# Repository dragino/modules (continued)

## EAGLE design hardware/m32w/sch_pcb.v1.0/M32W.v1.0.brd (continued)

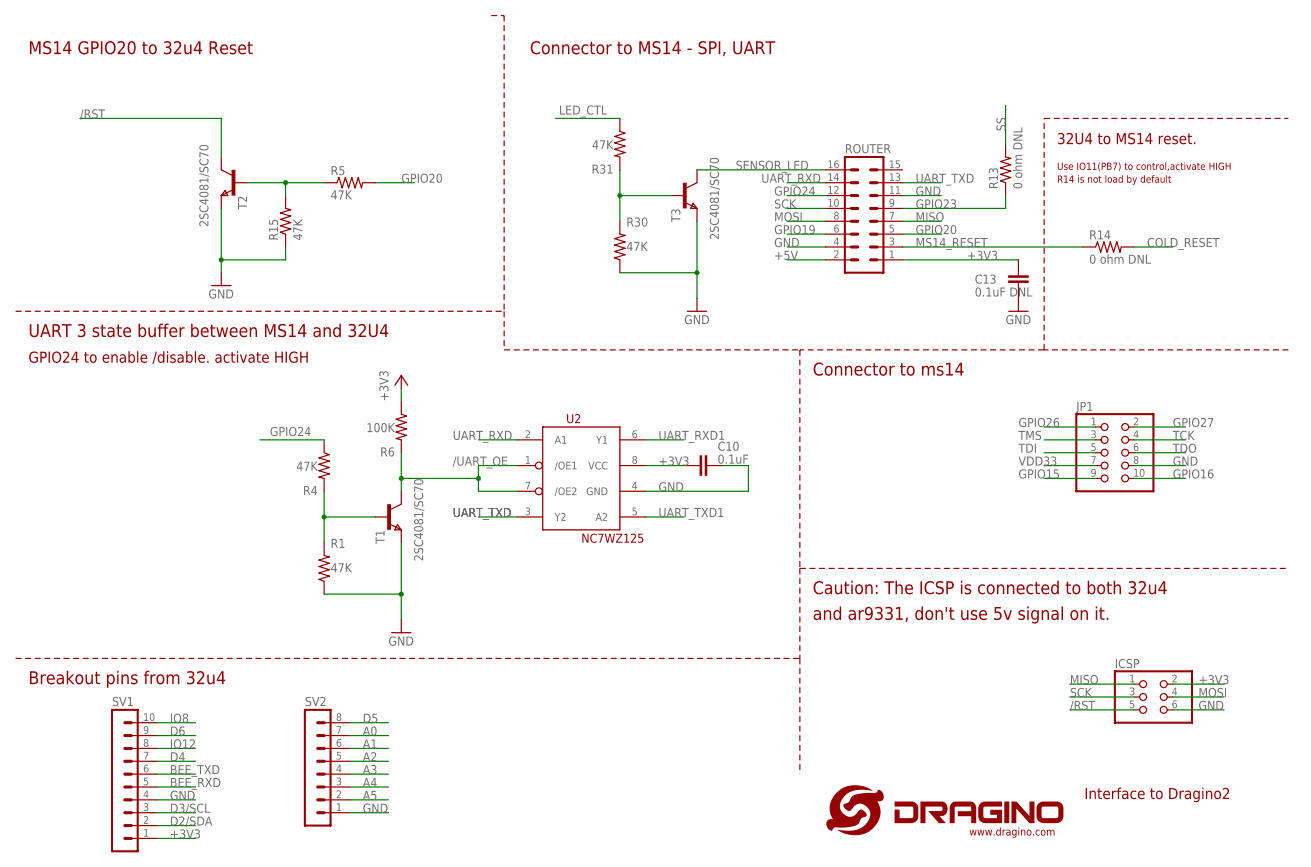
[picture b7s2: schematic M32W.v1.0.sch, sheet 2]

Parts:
C10: 0.1uF; C0402
C13: 0.1uF DNL; C0402
ICSP: PINHD-2X3; 2X03
JP1: PINHD-2X5_2.00; 2X05M
R1, R4, R5, R15, R30, R31: 47K; R0402
R6: 100K; R0402
R13, R14: 0 ohm DNL; R0402
ROUTER: MA08-2
SV1: MA10-1
SV2: MA08-1
T1, T3: 2SC4081/SC70; SOT323
T2: 2SC4081/SC70; SOT323; MPN DSS4160U-7
U2: NC7WZ125; US8
U$5: LOGO-NEW; LOGO-SILK-NEW

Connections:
+3V3: C10.2, C13.1, ICSP.2, R6.1, ROUTER.1, SV1.1, U2.8 (VCC); also elsewhere on the board
+5V: ROUTER.2
/RST: ICSP.5, T2.1 (C); also elsewhere on the board
/UART_OE: R6.2, T1.1 (C), U2.1 (/OE1), U2.7 (/OE2)
A0: SV2.7; also elsewhere on the board
A1: SV2.6; also elsewhere on the board
A2: SV2.5; also elsewhere on the board
A3: SV2.4; also elsewhere on the board
A4: SV2.3; also elsewhere on the board
A5: SV2.2; also elsewhere on the board
BEE_RXD: SV1.5; also elsewhere on the board
BEE_TXD: SV1.6; also elsewhere on the board
COLD_RESET: R14.2; also elsewhere on the board
D2/SDA: SV1.2; also elsewhere on the board
D3/SCL: SV1.3; also elsewhere on the board
D4: SV1.7; also elsewhere on the board
D5: SV2.8; also elsewhere on the board
D6: SV1.9; also elsewhere on the board
GND: C10.1, C13.2, ICSP.6, JP1.8, R1.1, R15.1, R30.1, ROUTER.4, ROUTER.11, SV1.4, SV2.1, T1.3 (E), T2.3 (E), T3.3 (E), U2.4 (GND); also elsewhere on the board
GPIO15: JP1.9
GPIO16: JP1.10
GPIO19: ROUTER.6
GPIO20: R5.2, ROUTER.5
GPIO23: R13.1, ROUTER.9
GPIO24: R4.1, ROUTER.12
GPIO26: JP1.1; also elsewhere on the board
GPIO27: JP1.2; also elsewhere on the board
IO8: SV1.10; also elsewhere on the board
IO12: SV1.8; also elsewhere on the board
LED_CTL: R31.1; also elsewhere on the board
MISO: ICSP.1, ROUTER.7; also elsewhere on the board
MOSI: ICSP.4, ROUTER.8; also elsewhere on the board
MS14_RESET: R14.1, ROUTER.3
unnamed: R1.2, R4.2, T1.2 (B)
unnamed: R5.1, R15.2, T2.2 (B)
unnamed: R30.2, R31.2, T3.2 (B)
SCK: ICSP.3, ROUTER.10; also elsewhere on the board
SENSOR_LED: ROUTER.16, T3.1 (C)
SS: R13.2; also elsewhere on the board
TCK: JP1.4
TDI: JP1.5
TDO: JP1.6
TMS: JP1.3
UART_RXD: ROUTER.14, U2.2 (A1); also elsewhere on the board
UART_RXD1: U2.6 (Y1); also elsewhere on the board
UART_TXD: ROUTER.13, U2.3 (Y2); also elsewhere on the board
UART_TXD1: U2.5 (A2); also elsewhere on the board
VDD33: JP1.7

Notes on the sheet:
UART 3 state buffer between MS14 and 32U4
Interface to Dragino2
Caution: The ICSP is connected to both 32u4
and ar9331, don't use 5v signal on it.
Connector to ms14
Connector to MS14 - SPI, UART
MS14 GPIO20 to 32u4 Reset
Breakout pins from 32u4
GPIO24 to enable /disable. activate HIGH
32U4 to MS14 reset.
Use IO11(PB7) to control,activate HIGH
R14 is not load by default

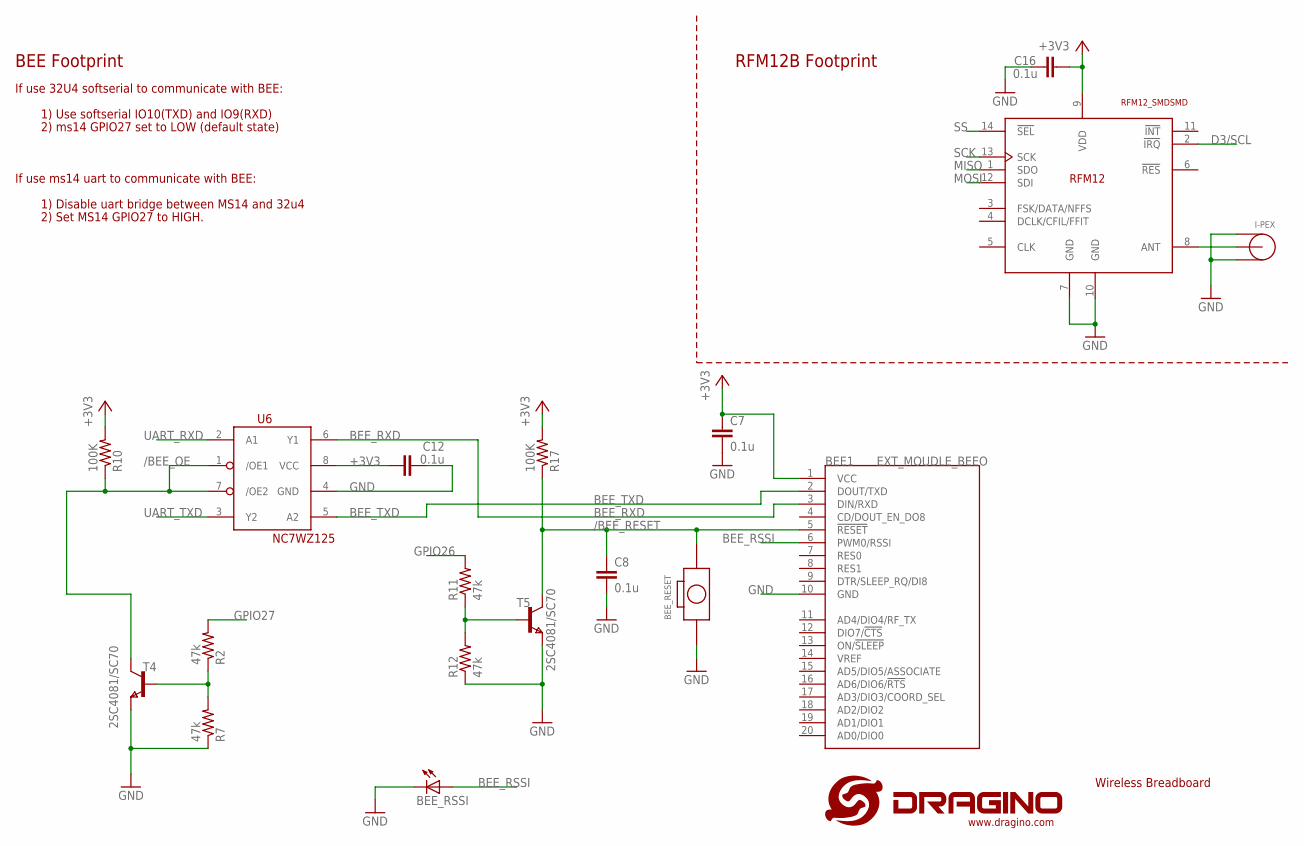
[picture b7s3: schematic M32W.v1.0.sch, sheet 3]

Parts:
BEE1: EXT_MOUDLE_BEEO; EXT_MOUDLE_BEE
BEE_RESET: CPT_SMD_BOTTON_1_SMD; CPT_SMD_BOTTON_1
BEE_RSSI: LEDCHIP-LED0805; CHIP-LED0805
C7, C8, C12, C16: 0.1u; C0402
I-PEX: I-PEX
R2, R7, R11, R12: 47k; R0402
R10, R17: 100K; R0402
T4, T5: 2SC4081/SC70; SOT323
U6: NC7WZ125; US8
U$3: RFM12_SMDSMD; RFM12

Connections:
+3V3: BEE1.1 (VCC), C7.1, C12.1, C16.2, R10.2, R17.2, U6.8 (VCC), U$3.9 (VDD); also elsewhere on the board
/BEE_OE: R10.1, T4.1 (C), U6.1 (/OE1), U6.7 (/OE2)
/BEE_RESET: BEE1.5 (!RESET), BEE_RESET.P$2 (2), C8.1, R17.1, T5.1 (C)
BEE_RSSI: BEE1.6 (PWM0/RSSI), BEE_RSSI.A
BEE_RXD: BEE1.3 (DIN/RXD), U6.6 (Y1); also elsewhere on the board
BEE_TXD: BEE1.2 (DOUT/TXD), U6.5 (A2); also elsewhere on the board
D3/SCL: U$3.2 (!IRQ); also elsewhere on the board
GND: BEE1.10 (GND), BEE_RESET.1, BEE_RSSI.C, C7.2, C8.2, C12.2, C16.1, I-PEX.GND, I-PEX.GND1, R7.1, R12.1, T4.3 (E), T5.3 (E), U6.4 (GND), U$3.7 (GND), U$3.10 (GND); also elsewhere on the board
GPIO26: R11.2; also elsewhere on the board
GPIO27: R2.2; also elsewhere on the board
MISO: U$3.1 (SDO); also elsewhere on the board
MOSI: U$3.12 (SDI); also elsewhere on the board
unnamed: R2.1, R7.2, T4.2 (B)
unnamed: R11.1, R12.2, T5.2 (B)
unnamed: I-PEX.SIG, U$3.8 (ANT)
SCK: U$3.13 (SCK); also elsewhere on the board
SS: U$3.14 (!SEL); also elsewhere on the board
UART_RXD: U6.2 (A1); also elsewhere on the board
UART_TXD: U6.3 (Y2); also elsewhere on the board

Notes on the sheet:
Wireless Breadboard
RFM12B Footprint
BEE Footprint
If use 32U4 softserial to communicate with BEE:
1) Use softserial IO10(TXD) and IO9(RXD)
2) ms14 GPIO27 set to LOW (default state)
If use ms14 uart to communicate with BEE:
1) Disable uart bridge between MS14 and 32u4
2) Set MS14 GPIO27 to HIGH.

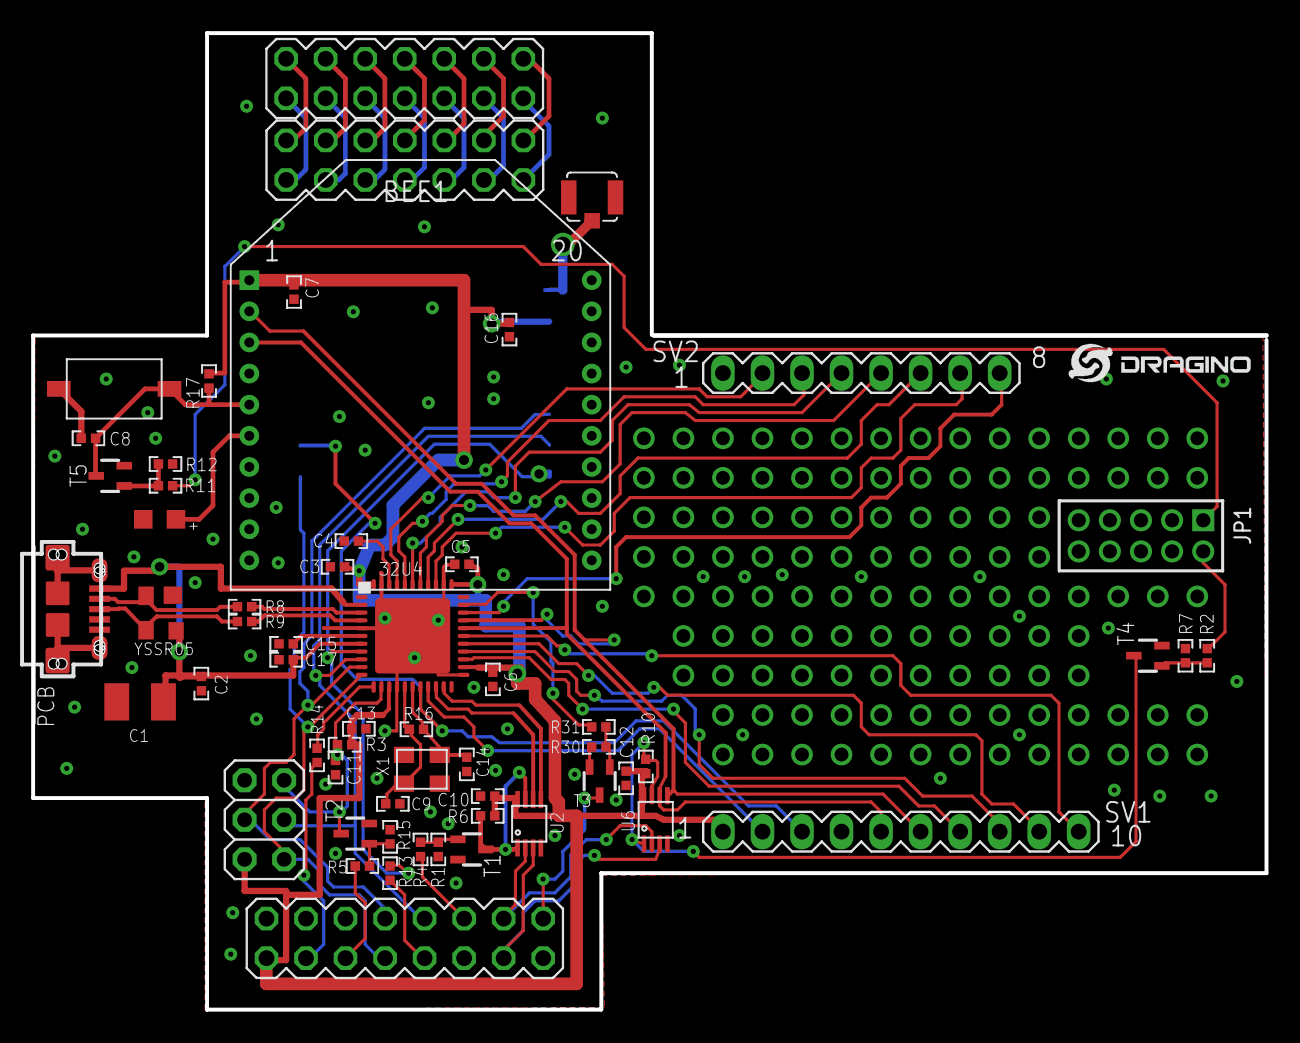
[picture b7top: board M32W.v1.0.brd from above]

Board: 2 copper layers, 79.2 x 62.7 mm, 60 parts (1 on the bottom side), 68 nets.

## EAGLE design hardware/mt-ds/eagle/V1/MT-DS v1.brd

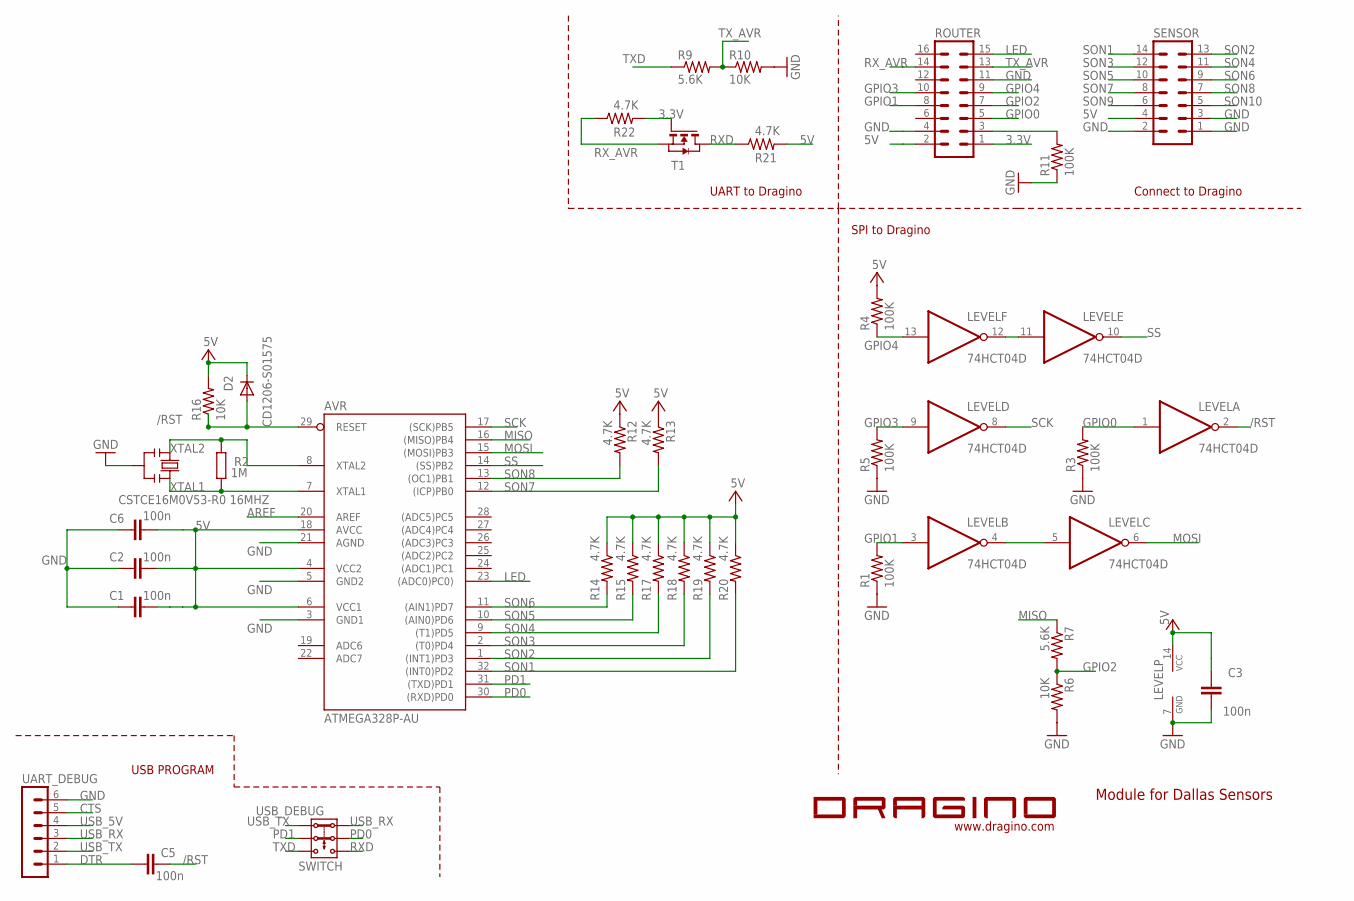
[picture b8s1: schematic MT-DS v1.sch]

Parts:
AVR: ATMEGA328P-AU; SMARTPRJ_TQFP32-08
C1, C2, C3, C5, C6: 100n; C0402
D2: CD1206-S01575; MINIMELF
LEVEL: 74HCT04D; SO14
R1, R3, R4, R5, R11: 100K; R0402
R2: 1M; R0402
R6, R10, R16: 10K; R0402
R7, R9: 5.6K; R0402
R12, R13, R14, R15, R17, R18, R19, R20, R21, R22: 4.7K; R0805
ROUTER: MA08-2
SENSOR: MA07-2
T1: NMOSFET-SOT23; SOT-23
U$1: LOGO-SILK; LOGO-SILK-15MM
UART_DEBUG: MA06-1
USB_DEBUG: SWITCH; 2P2T
Y2: CSTCE16M0V53-R0 16MHZ; RESONATOR

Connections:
3.3V: R22.2, ROUTER.1, T1.3 (G)
5V: AVR.4 (VCC2), AVR.6 (VCC1), AVR.18 (AVCC), C1.1, C2.1, C3.2, C6.1, D2.C, LEVEL.14 (VCC), R4.2, R12.1, R13.1, R14.1, R15.1, R16.2, R17.1, R18.1, R19.1, R20.1, R21.2, ROUTER.2, SENSOR.4
/RST: AVR.29 (RESET), C5.2, D2.A, LEVEL.2 (O), R16.1
AREF: AVR.20 (AREF)
CTS: UART_DEBUG.5
DTR: C5.1, UART_DEBUG.1
GND: AVR.3 (GND1), AVR.5 (GND2), AVR.21 (AGND), C1.2, C2.2, C3.1, C6.2, LEVEL.7 (GND), R1.1, R3.1, R5.1, R6.2, R10.2, R11.1, ROUTER.4, ROUTER.11, SENSOR.1, SENSOR.2, SENSOR.3, UART_DEBUG.6, Y2.2
GPIO0: LEVEL.1 (I), R3.2, ROUTER.5
GPIO1: LEVEL.3 (I), R1.2, ROUTER.8
GPIO2: R6.1, R7.2, ROUTER.7
GPIO3: LEVEL.9 (I), R5.2, ROUTER.10
GPIO4: LEVEL.13 (I), R4.1, ROUTER.9
LED: AVR.23 ((ADC0)PC0)), ROUTER.15
MISO: AVR.16 ((MISO)PB4), R7.1
MOSI: AVR.15 ((MOSI)PB3), LEVEL.6 (O)
unnamed: R11.2, ROUTER.3
unnamed: LEVEL.11 (I), LEVEL.12 (O)
unnamed: LEVEL.4 (O), LEVEL.5 (I)
PD0: AVR.30 ((RXD)PD0), USB_DEBUG.2.1
PD1: AVR.31 ((TXD)PD1), USB_DEBUG.2.2
RXD: R21.1, T1.1 (D), USB_DEBUG.3.1
RX_AVR: R22.1, ROUTER.14, T1.2 (S)
SCK: AVR.17 ((SCK)PB5), LEVEL.8 (O)
SON1: AVR.32 ((INT0)PD2), R20.2, SENSOR.14
SON2: AVR.1 ((INT1)PD3), R19.2, SENSOR.13
SON3: AVR.2 ((T0)PD4), R18.2, SENSOR.12
SON4: AVR.9 ((T1)PD5), R17.2, SENSOR.11
SON5: AVR.10 ((AIN0)PD6), R15.2, SENSOR.10
SON6: AVR.11 ((AIN1)PD7), R14.2, SENSOR.9
SON7: AVR.12 ((ICP)PB0), R13.2, SENSOR.8
SON8: AVR.13 ((OC1)PB1), R12.2, SENSOR.7
SON9: SENSOR.6
SON10: SENSOR.5
SS: AVR.14 ((SS)PB2), LEVEL.10 (O)
TXD: R9.1, USB_DEBUG.3.2
TX_AVR: R9.2, R10.1, ROUTER.13
USB_5V: UART_DEBUG.4
USB_RX: UART_DEBUG.3, USB_DEBUG.1.1
USB_TX: UART_DEBUG.2, USB_DEBUG.1.2
XTAL1: AVR.7 (XTAL1), R2.1, Y2.3
XTAL2: AVR.8 (XTAL2), R2.2, Y2.1

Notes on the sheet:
Connect to Dragino
SPI to Dragino
UART to Dragino
USB PROGRAM
Module for Dallas Sensors

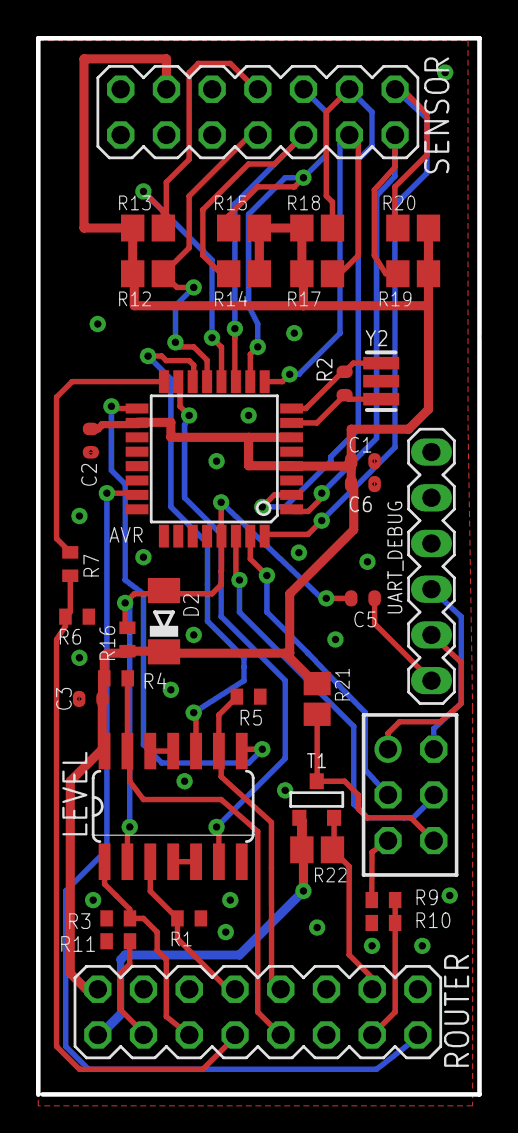
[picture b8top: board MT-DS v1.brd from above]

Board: 2 copper layers, 24.5 x 58.7 mm, 36 parts (0 on the bottom side), 36 nets.

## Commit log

2013-09-17 move files from dragino svn to git
2013-10-02 Add MS14 Bridge Example for Arduino Yun
2013-10-05 Add bridge example
2013-10-06 Add tested examples
    All are tested with ms14 + Lenonard
2013-10-07 Add Tested Example for Yun
2013-10-15 Add Tested Example for demo Yun + RFM12B
2013-10-16 Update Xively / Yeelink examples
    New example works with mega168 as well. Try to call linux script to
    upload sensor data.
2013-11-21 update sketch to better fit mrfm12b
2013-11-22 Add Sensor Projects
2013-11-25 update datalog example
2013-11-27 add example
    example: use a switch to control remote relay
2013-12-01 add m32 source
2013-12-06 Example to send daily report via Email
2013-12-06 ooops
2013-12-07 miss two pages.
2013-12-11 Serial LCD example- Remote control
    use REST calls to control a LCD
2014-01-21 Add M32 Silkscreen
2014-02-10 Add Cumulocity Client Demo
2014-02-24 add Cumulocity Get Alarm, Set Alarm Example
2014-02-24 Update Temperature_Humidity_to_Cumulocity.ino
    remove \" \" for single word. \" only require for the sentences with space in between. such as "\"Over Heated\""
2014-03-13 Add M32W Sketch examples
    RFM12B and XBee
2014-04-01 Add EMG sensor and NeoMatrix example
2014-04-04 Improve Layout
2014-04-16 Upload Bluetooth Example
2014-04-16 Add M32W hardware source
2014-04-23 Update RF reader and nRF24L01 examples for m32w
2014-04-25 Upload Test Sketch
2014-07-09 Upload Yun Shield Source
2014-07-09 add bom
2014-07-24 Add HE Start Kit
    A reference design for HE.
2014-07-24 modify Yun Shield suffix
2014-11-16 add m328w rfm12b example
2014-11-29 upload examples
2014-12-01 update bee converter info
2014-12-02 With Serial I could not see the output. I am using Dragino MS14-P with M32W. Console is compatible with Serial, so I replaced it and the output is visible to the Serial Monitor of Arduino IDE.
2014-12-02 there was a problem with the curly brackets. Even when the whole string is tested on ssh at the Dragino, the curl had a problem with the curly brackets. -g parameter helped the curl process sends jso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
    -g, --globoff
    This option switches off the "URL globbing parser". When you set this option, you can specify URLs that contain the letters {}[] without having them being interpreted by curl itself. Note that these 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
2015-01-06 Add RF69 Demo Code
2015-01-08 Update M328W hardware file
2015-01-20 Add hardware platform in Arduino IDE
    Thanks for Nico Hood (http://www.nicohood.de) providing these.
2015-04-27 add board.txt
2015-08-15 Add Yun Shield V1.1 hardware files
2015-10-26 add new hardware source for Yun Shield and Yun Shield Teensy adapter
2016-05-03 Update Yun Shield and PoE injector hardware files
2016-05-24 Add Yun Shield v2.4 hardware Files
    Add Yun Shield v2.4 hardware Files
2016-11-25 update ms14n hardware source
2017-01-09 add v1.2 hardware source
2017-08-22 Add FXS module
